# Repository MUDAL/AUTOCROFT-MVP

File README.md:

# AUTOCROFT-MVP

Autocroft is an automatic irrigation system designed and developed by **IoTeam**.

This codebase is an improved Master-Node Architecture based on one master and several base nodes.  
The base nodes collect data and forward them to the master.  
The master processes data from multiple base nodes and sends to the cloud.  

Some **keypad** functionalities:  
- A:  Forward  
- B:  Backward  
- C:  Up/Down  
- D:  Clear memory/Reset system  
- #:  Select 
- *:  Send data from master to the nodes

# Tested versions  
Version 1.0 and Version 1.1 
Each node will be assigned a subchannel of the 433MHz 
communication system. The master will switch from channel to channel in order to send and receive 
data from the nodes.

# How it works  
The master sends data to the nodes in order for them to make irrigation decisions. Irrigation decisions are made  
once every hour (under automatic control). The master and nodes have a runtime of 26 minutes and they sleep for  
34 minutes every hour.  

# Version 1.1  
Has similar features with version 1.0 but with the following changes:  
1. No Bluetooth and WiFi in the master controller.  
2. No EEPROM in the Nodes.  
3. Use of LCD with I2C GPIO expander for the master controller.  

# Link to documentation  
https://www.researchgate.net/publication/359510238_DESIGN_OF_A_LOW_POWER_AUTOMATIC_IRRIGATION_SYSTEM  

# Prototype  

# 3D models of prototype PCB

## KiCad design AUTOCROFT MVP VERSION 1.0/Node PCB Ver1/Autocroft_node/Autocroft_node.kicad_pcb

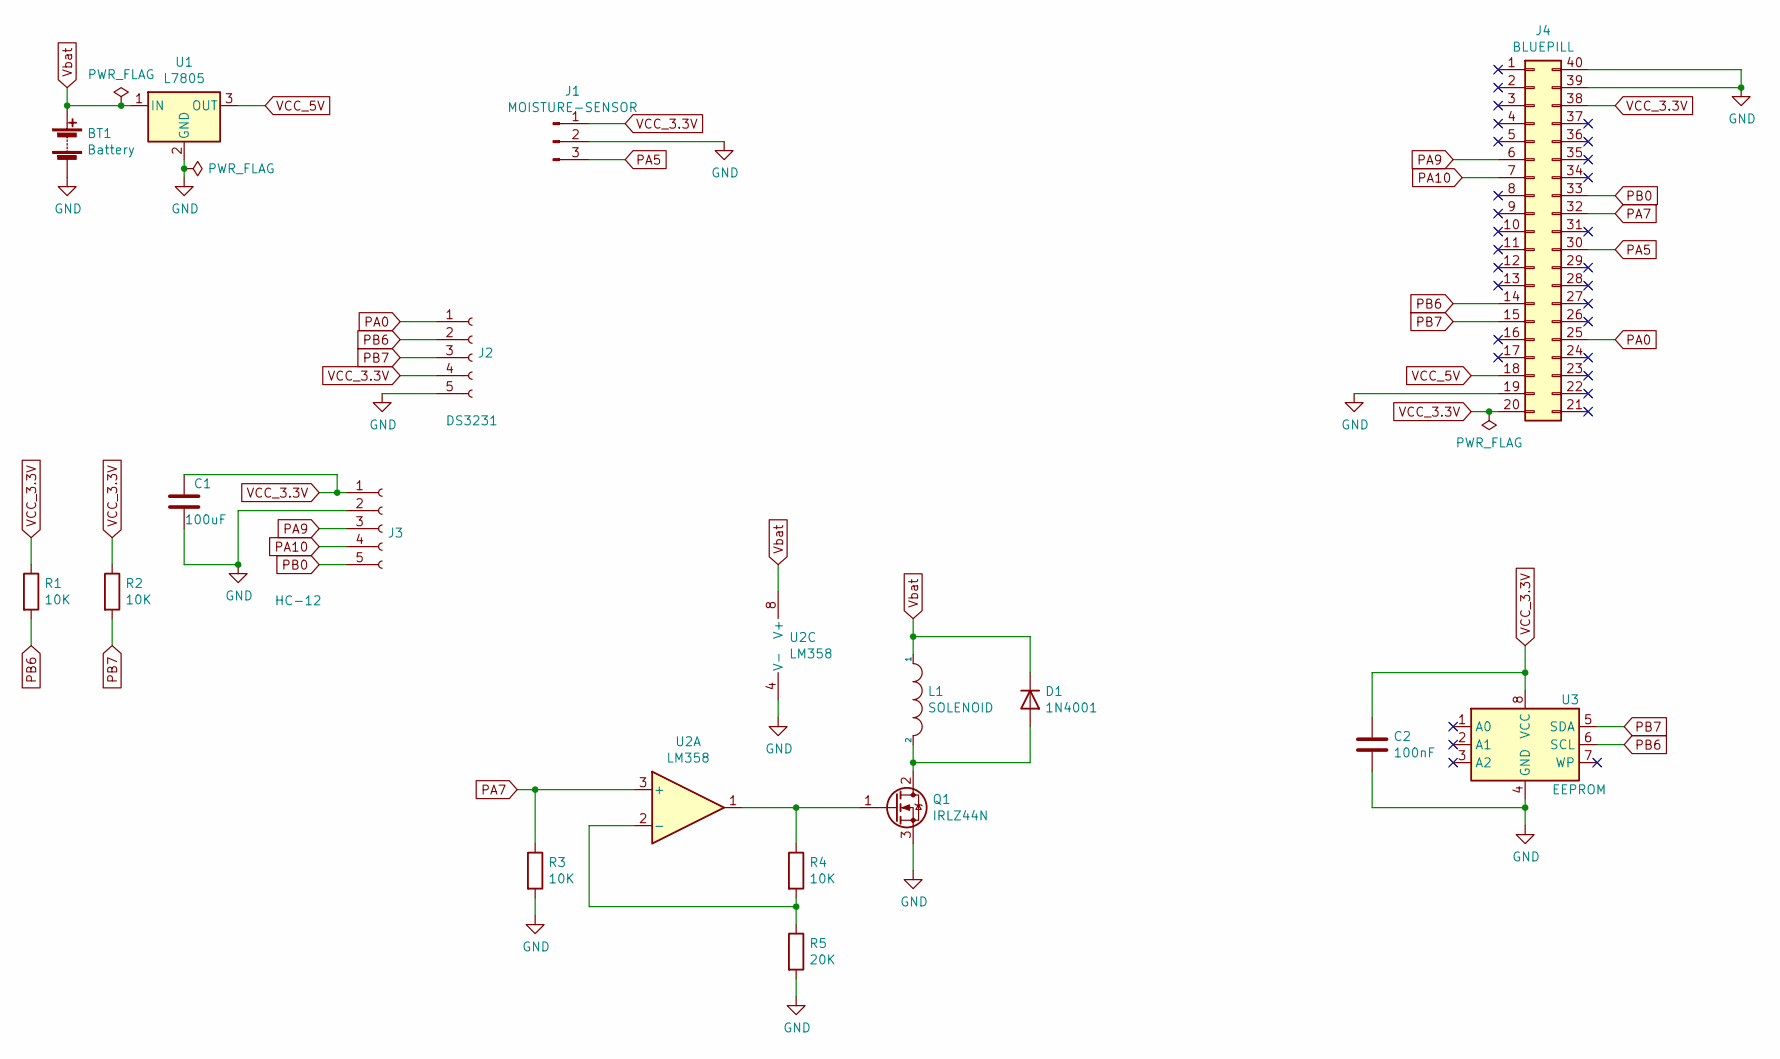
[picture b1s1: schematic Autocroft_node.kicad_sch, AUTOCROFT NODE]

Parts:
BT1: Battery; BATT
C1: 100uF; CP_Radial_D10.0mm_P5.00mm
C2: 100nF; C_Disc_D3.0mm_W2.0mm_P2.50mm
D1: 1N4001; D_DO-41_SOD81_P10.16mm_Horizontal
J1: MOISTURE-SENSOR; PinHeader_1x03_P2.54mm_Vertical
J2: DS3231; PinSocket_1x05_P2.54mm_Vertical
J3: HC-12; PinSocket_1x05_P2.54mm_Vertical
J4: BLUEPILL
L1: SOLENOID; BATT
Q1: IRLZ44N; TO-220-3_Vertical
R1, R2, R3, R4: 10K; R_Axial_DIN0207_L6.3mm_D2.5mm_P7.62mm_Horizontal
R5: 20K; R_Axial_DIN0207_L6.3mm_D2.5mm_P7.62mm_Horizontal
U1: L7805; TO-220-3_Vertical
U2: LM358; DIP-8_W7.62mm_Socket
U3: EEPROM; DIP-8_W7.62mm_Socket

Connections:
GND: BT1.2 (-), C1.2, C2.2, J1.2, J2.5, J3.2, J4.19, J4.39, J4.40, Q1.3 (S), R3.2, R5.2, U1.2 (GND), U2.4 (V-), U3.4 (GND)
unnamed: D1.2 (A), L1.2, Q1.2 (D)
unnamed: Q1.1 (G), R4.1, U2.1
unnamed: R4.2, R5.1, U2.2 (-)
PA0: J2.1, J4.25
PA5: J1.3, J4.30
PA7: J4.32, R3.1, U2.3 (+)
PA9: J3.3, J4.6
PA10: J3.4, J4.7
PB0: J3.5, J4.33
PB6: J2.2, J4.14, R1.2, U3.6 (SCL)
PB7: J2.3, J4.15, R2.2, U3.5 (SDA)
VCC_3.3V: C1.1, C2.1, J1.1, J2.4, J3.1, J4.20, J4.38, R1.1, R2.1, U3.8 (VCC)
VCC_5V: J4.18, U1.3 (OUT)
Vbat: BT1.1 (+), D1.1 (K), L1.1, U1.1 (IN), U2.8 (V+)

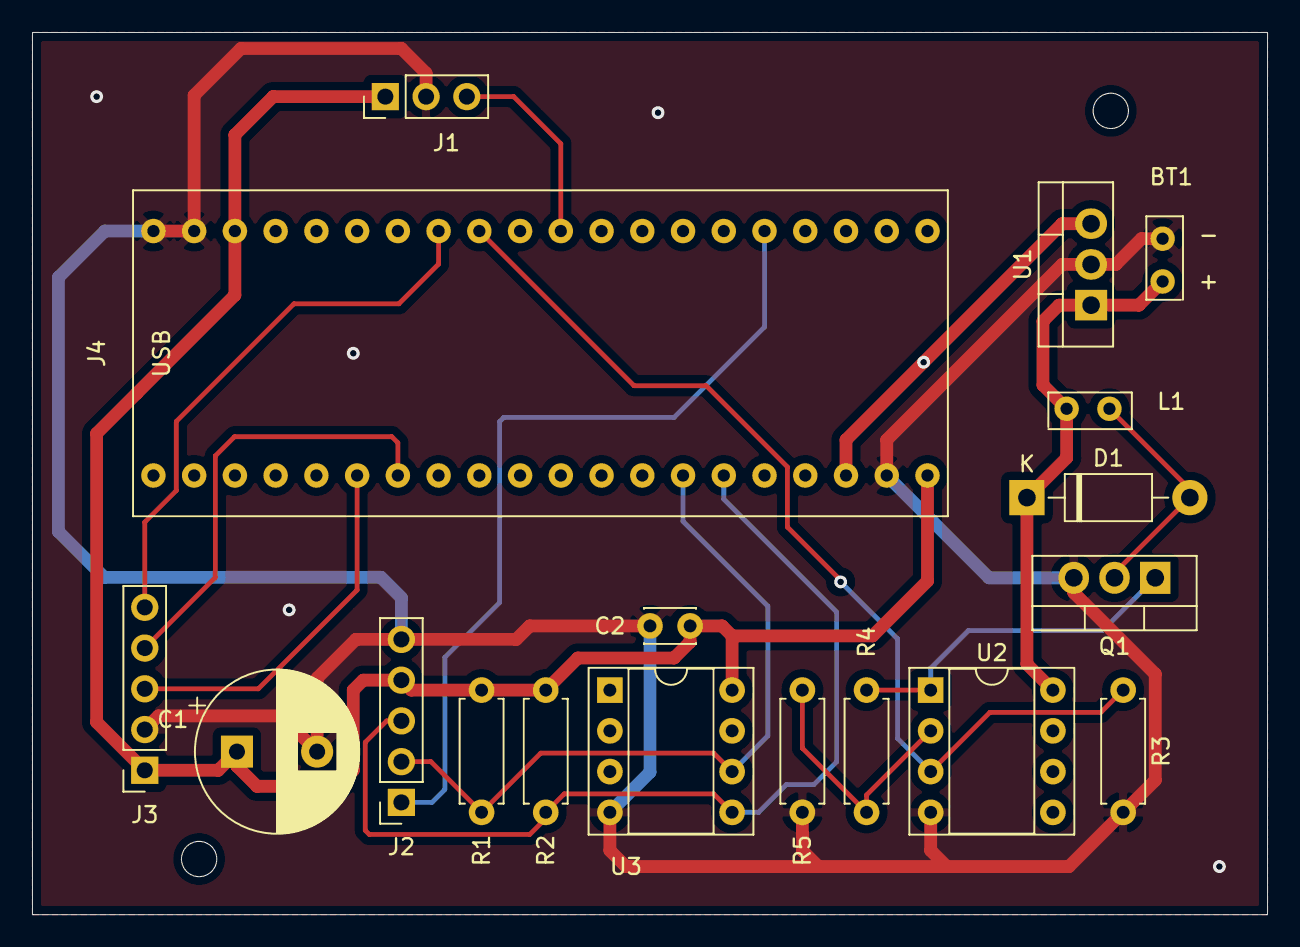
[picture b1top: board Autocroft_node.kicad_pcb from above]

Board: 2 copper layers, 77.0 x 55.0 mm, 20 parts (0 on the bottom side), 15 nets.

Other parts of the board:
 : MountingHole_2.2mm_M2
 #2: MountingHole_2.2mm_M2

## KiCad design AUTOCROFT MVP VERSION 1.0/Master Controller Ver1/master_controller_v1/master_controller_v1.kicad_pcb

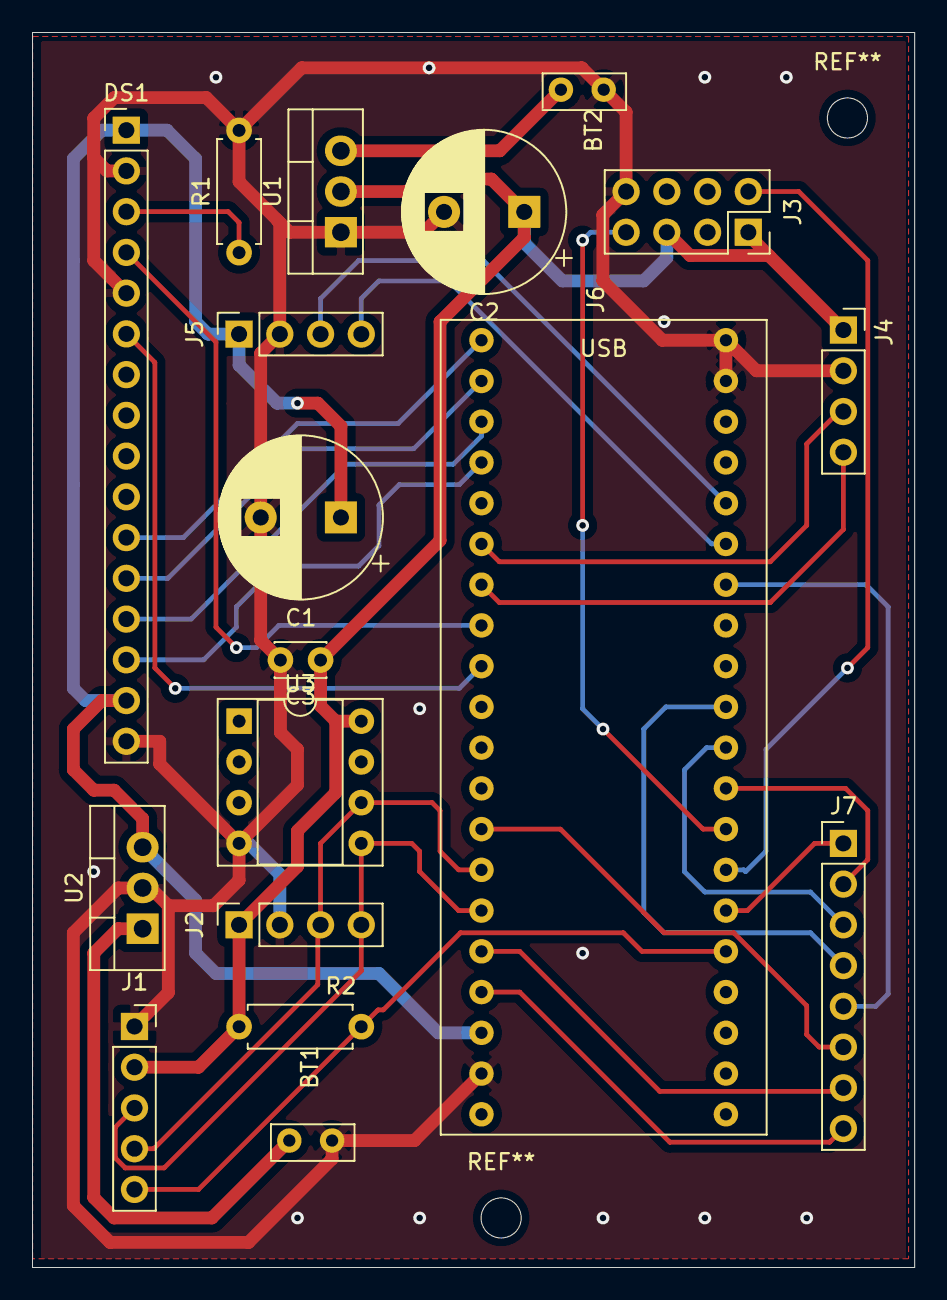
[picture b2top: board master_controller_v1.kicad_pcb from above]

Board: 2 copper layers, 55.0 x 77.0 mm, 18 parts (0 on the bottom side), 29 nets.

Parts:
BT1, BT2: 2 Li-ion (7.4V); BATT
C1, C2: 100uF; CP_Radial_D10.0mm_P5.00mm
C3: 100nF; C_Disc_D3.0mm_W2.0mm_P2.50mm
DS1: LCD1602; PinHeader_1x16_P2.54mm_Vertical
J1: DS3231; PinSocket_1x05_P2.54mm_Vertical
J2: BME280; PinSocket_1x04_P2.54mm_Vertical
J3: ESP8266; PinSocket_2x04_P2.54mm_Vertical
J4: HC12; PinSocket_1x04_P2.54mm_Vertical
J5: HC06; PinSocket_1x04_P2.54mm_Vertical
J6: STM32 Bluepill; BLUEPILL
J7: Keypad; PinHeader_1x08_P2.54mm_Vertical
R1: 1k; R_Axial_DIN0207_L6.3mm_D2.5mm_P7.62mm_Horizontal
R2: 10k; R_Axial_DIN0207_L6.3mm_D2.5mm_P7.62mm_Horizontal
U1: LM1117-3.3; TO-220-3_Vertical
U2: LM7805_TO220; TO-220-3_Vertical
U3: EEPROM; DIP-8_W7.62mm_Socket

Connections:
GND: BT1.2, BT2.2, C1.2, C2.2, C3.2, DS1.2, DS1.5, DS1.16, J1.1, J2.2, J3.8, J4.2, J5.2, J6.19, J6.39, J6.40, R1.2, U1.1, U2.2, U3.4
unnamed: BT1.1, U2.1
unnamed: BT2.1, U1.3
unnamed: DS1.3, R1.1
PA0: J1.5, J6.25, R2.1
PA1: J6.26, J7.1
PA2: J3.2, J6.27
PA3: J3.7, J6.28
PA4: J6.29, J7.2
PA5: J6.30, J7.3
PA6: J6.31, J7.4
PA9: J4.3, J6.6
PA10: J4.4, J6.7
PA11: DS1.4, J6.8
PA12: DS1.6, J6.9
PB1: J6.34, J7.5
PB5: J6.13, J7.6
PB6: J1.4, J2.3, J6.14, U3.6
PB7: J1.3, J2.4, J6.15, U3.5
PB8: J6.16, J7.7
PB9: J6.17, J7.8
PB10: J5.4, J6.35
PB11: J5.3, J6.36
PB12: DS1.11, J6.1
PB13: DS1.12, J6.2
PB14: DS1.13, J6.3
PB15: DS1.14, J6.4
VCC_3V3: C2.1, C3.1, J1.2, J2.1, J3.1, J3.5, J4.1, R2.2, U1.2, U3.8
VCC_5V: C1.1, DS1.1, DS1.15, J5.1, J6.18, U2.3

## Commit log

2021-04-05 optimized the state machine a bit
2021-04-05 FSM optimization
2021-04-11 DS3231 PCB design
    The DS3231 module is used for real-time synchronization of nodes in an Autocroft network
2021-04-11 DS3231 PCB design.
    DS3231 RTC module is used for real-time synchronization of nodes in an Autocroft network.
2021-07-18 New changes
    Changes to names of files and folders. Organization of documents
2021-07-19 Removed redundant configuration
2021-07-19 Keep PA0 default state
2021-07-19 Removed Potentiometer
2021-07-19 Master Controller PCB V1
2021-07-20 More mods
2021-07-20 Additional updates
2021-07-20 Improved Naming
2021-07-20 Progress in design
2021-07-21 Complete design
2021-07-21 Improved Silkscreen Placement
2021-07-21 Updated Images
2021-07-22 removed
2021-07-22 keypad
    Interfacing the blue-pill with 4x4 keypad
2021-07-23 Updated software
2021-07-23 changed int to uint8_t
2021-07-23 Increased keypad delay by 20ms
2021-07-23 Rearranged order to #includes
2021-07-26 HC12 SET Pin
    For channel selection
2021-07-27 Autocroft Node
2021-07-27 HC12 Redesign
    Accomodation of 'SET' pin for future software versions and testing.
2021-07-27 Design changed
2021-07-28 Node PCB
2021-07-28 folder renamed
2021-08-07 Adjusted code
2021-08-08 added STEP files
2021-08-08 adc changes
2021-08-12 Bill of Materials
2021-08-12 updated code (added IDLE LINE)
2021-08-12 code to be tested
2021-08-13 updated code
2021-08-13 ADC tStab delay
2021-08-22 updated schematic
2021-08-22 important updates
    successfully tested
2021-08-23 workable updates
2021-08-24 Significant update
2021-08-24 more updates
2021-08-25 code update
2021-08-25 tested code
2021-10-01 Features to be added in the next version
2021-12-10 Update fp-info-cache
2021-12-10 Version 1.1
2021-12-11 tested codes
2021-12-12 functional
